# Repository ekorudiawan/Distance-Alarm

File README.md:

# Distance-Alarm
Simple Distance Alarm Using Ultrasonic Sensor

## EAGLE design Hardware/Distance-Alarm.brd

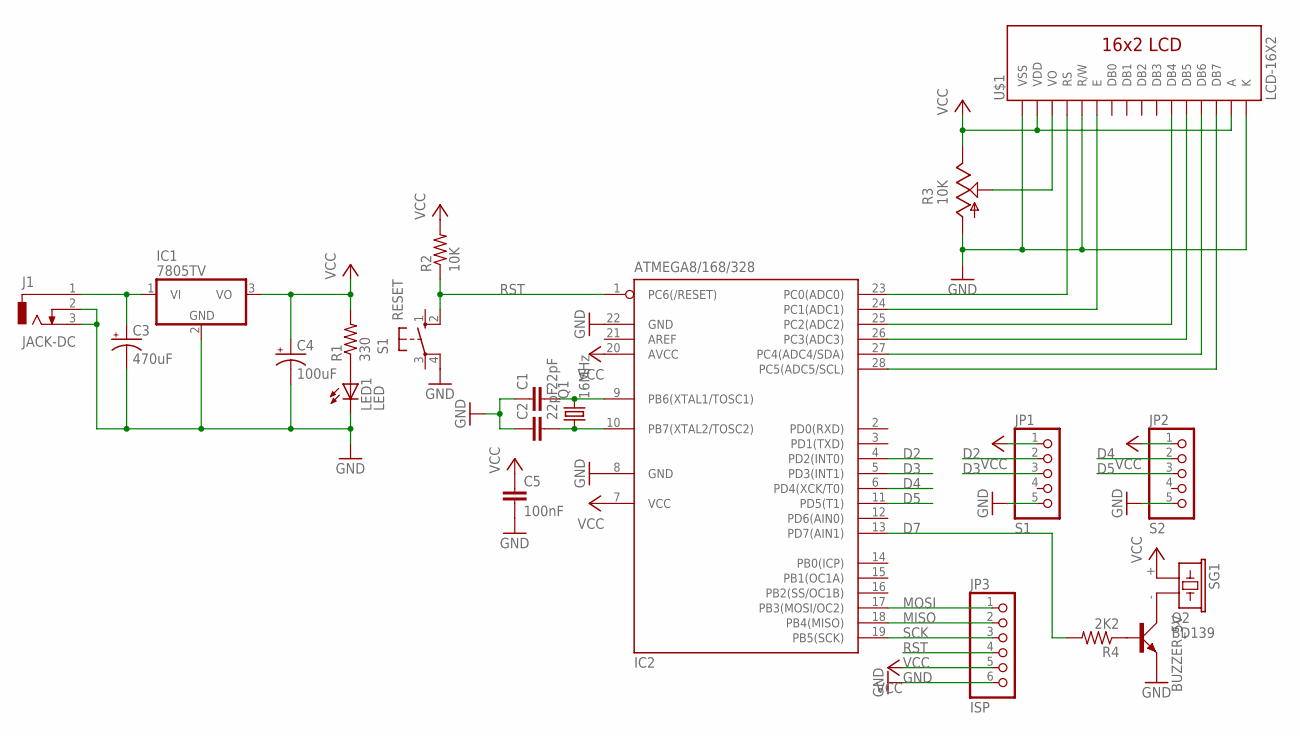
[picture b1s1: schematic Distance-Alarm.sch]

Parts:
C1, C2: 22pF; C025-024X044
C3: 470uF; E2,5-6
C4: 100uF; E2,5-6
C5: 100nF; C025-024X044
IC1: 7805TV; TO220V
IC2: ATMEGA8/168/328; DIL28-3
J1: JACK-DC; DCJ0202
JP1: S1; 1X05
JP2: S2; 1X05
JP3: ISP; 1X06
LED1: LED; LED3MM
Q1: 16MHz; HC49/S
Q2: BD139; TO126AV
R1: 330; 0207/10
R2: 10K; 0207/10
R3: 10K; CA6V
R4: 2K2; 0207/10
S1: RESET; B3F-10XX
SG1: BUZZER_5V; BUZZER_F/CM12P
U$1: LCD-16X2

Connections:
D2: IC2.4 (PD2(INT0)), JP1.2
D3: IC2.5 (PD3(INT1)), JP1.3
D4: IC2.6 (PD4(XCK/T0)), JP2.2
D5: IC2.11 (PD5(T1)), JP2.3
D7: IC2.13 (PD7(AIN1)), R4.2
GND: C1.1, C2.1, C3.-, C4.-, C5.2, IC1.2 (GND), IC2.8 (GND), IC2.22 (GND), J1.2, J1.3, JP1.5, JP2.5, JP3.6, LED1.K (C), Q2.E, R3.A, S1.4 (P1), U$1.1 (VSS), U$1.5 (R/W), U$1.16 (K)
MISO: IC2.18 (PB4(MISO)), JP3.2
MOSI: IC2.17 (PB3(MOSI/OC2)), JP3.1
unnamed: C3.+, IC1.1 (VI), J1.1
unnamed: IC2.23 (PC0(ADC0)), U$1.4 (RS)
unnamed: LED1.A, R1.1
unnamed: R3.S, U$1.3 (VO)
unnamed: IC2.24 (PC1(ADC1)), U$1.6 (E)
unnamed: C1.2, IC2.9 (PB6(XTAL1/TOSC1)), Q1.2
unnamed: C2.2, IC2.10 (PB7(XTAL2/TOSC2)), Q1.1
unnamed: IC2.25 (PC2(ADC2)), U$1.11 (DB4)
unnamed: IC2.26 (PC3(ADC3)), U$1.12 (DB5)
unnamed: IC2.27 (PC4(ADC4/SDA)), U$1.13 (DB6)
unnamed: IC2.28 (PC5(ADC5/SCL)), U$1.14 (DB7)
unnamed: Q2.C, SG1.- (2)
unnamed: Q2.B, R4.1
RST: IC2.1 (PC6(/RESET)), JP3.4, R2.1, S1.2 (S1)
SCK: IC2.19 (PB5(SCK)), JP3.3
VCC: C4.+, C5.1, IC1.3 (VO), IC2.7 (VCC), IC2.20 (AVCC), JP1.1, JP2.1, JP3.5, R1.2, R2.2, R3.E, SG1.+ (1), U$1.2 (VDD), U$1.15 (A)

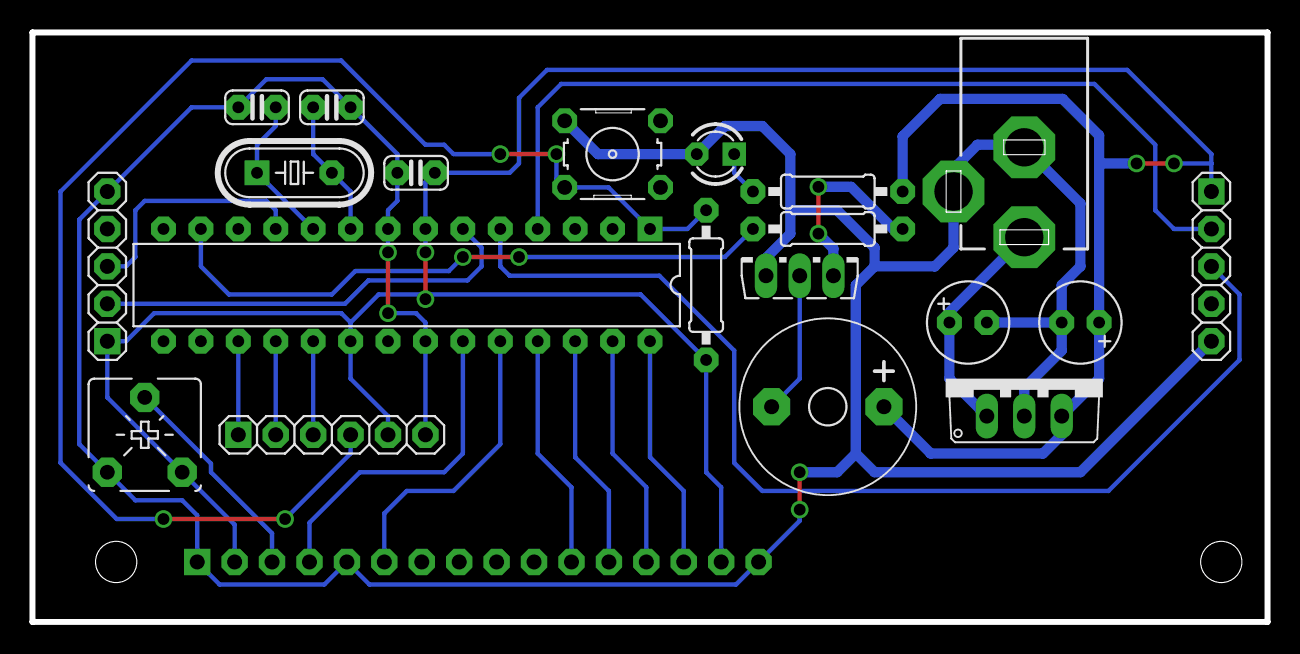
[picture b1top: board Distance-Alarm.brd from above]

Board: 2 copper layers, 83.8 x 40.0 mm, 21 parts (0 on the bottom side), 24 nets.

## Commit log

2017-10-03 Added HW & SW Files
